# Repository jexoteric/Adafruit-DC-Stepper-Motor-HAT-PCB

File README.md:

# Raspberry Pi Zero DC and Stepper motor hat
Creating a more compact version of the Adafruit DC Stepper motor hat, with the goal of 100% compatability. The only real changes are there is no prototyping area or breakout of the pi pins. Optionally, the four extra PWM pins are now set up to control servos, using a seperate 5V power supply.

Programming with this board should be 100% identical to programming with the original Adafruit design linked below.

For more details, check out the product page at

   * https://www.adafruit.com/products/2348

Adafruit invests time and resources providing this open source design, 
please support Adafruit and open-source hardware by purchasing 
products from Adafruit!

Original board designed by Adafruit Industries.  
Creative Commons Attribution, Share-Alike license, check license.txt for more information
All text above must be included in any redistribution

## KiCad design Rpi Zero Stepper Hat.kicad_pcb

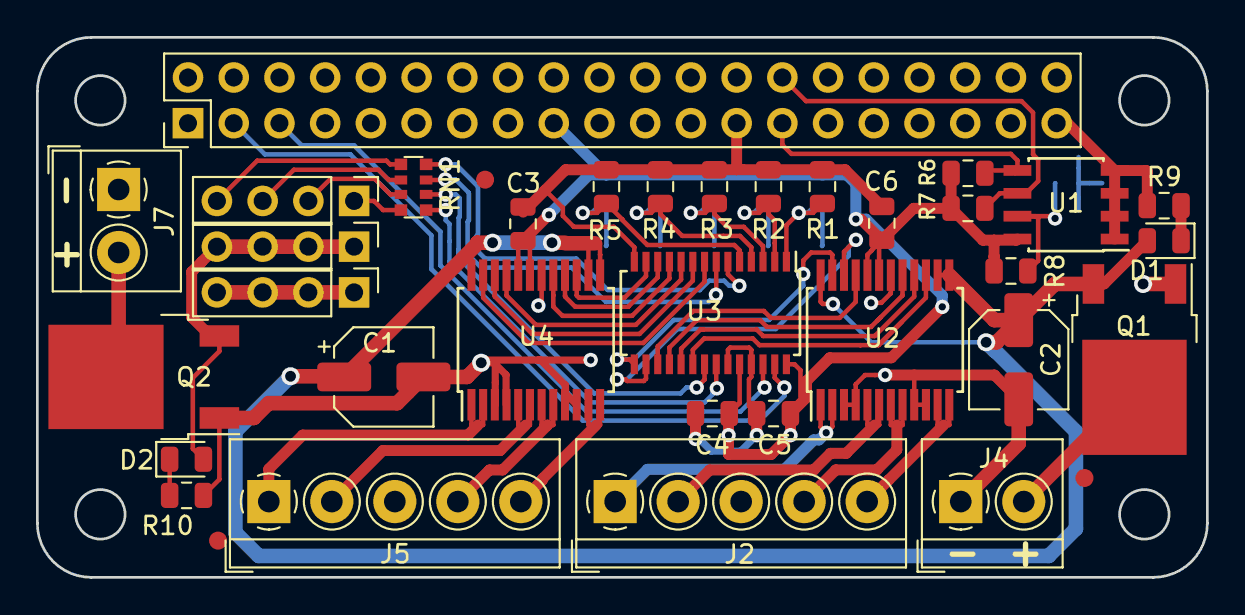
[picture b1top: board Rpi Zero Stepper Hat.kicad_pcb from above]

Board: 2 copper layers, 65.0 x 30.0 mm, 44 parts (0 on the bottom side), 46 nets.

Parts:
+: Conn_01x05_Male; PinHeader_1x04_P2.54mm_Vertical
C1, C2: 47uF/16v; CP_Elec_5x5.4
C3, C6: 10uF; C_0805_2012Metric
C4, C5: 0.1uF; C_0805_2012Metric
D1, D2: GREEN; D_0805_2012Metric
G: Conn_01x04_Male; PinHeader_1x04_P2.54mm_Vertical
J1: Raspberry_Pi_2_3; PinHeader_2x20_P2.54mm_Vertical
J2, J5: Screw_Terminal_01x05; TerminalBlock_4Ucon_1x05_P3.50mm_Horizontal
J3: Conn_01x04_Male; PinHeader_1x04_P2.54mm_Vertical
J4, J7: Screw_Terminal_01x02; TerminalBlock_4Ucon_1x02_P3.50mm_Horizontal
JP1, JP2, JP3, JP4, JP5: SolderJumper_2_Open; SolderJumper-2_P1.3mm_Open_Pad1.0x1.5mm
JP6: SolderJumper_2_Bridged; SolderJumper-2_P1.3mm_Bridged_RoundedPad1.0x1.5mm
Q1, Q2: AOD417; TO-252-2
R1, R2, R3, R4, R5: 10K; R_0805_2012Metric
R6, R7, R8: 3.9K; R_0805_2012Metric
R9: 1K; R_0805_2012Metric
R10: 300; R_0805_2012Metric
RN1: R_Pack04; R_Array_Convex_4x0612
TP1, TP2, TP3, TP4, TP5: TestPoint; TestPoint_Pad_D2.0mm
U1: CAT24C32; SOIC-8_3.9x4.9mm_P1.27mm
U2, U4: TB6612FNG; SSOP-24_5.3x8.2mm_P0.65mm
U3: PCA9685PW; TSSOP-28_4.4x9.7mm_P0.65mm

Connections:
+3V3: C3.1, C4.1, C5.1, C6.1, J1.1, J1.17, JP1.2, JP2.2, JP3.2, JP4.2, JP5.2, R6.2, R7.1, R8.1, U1.8, U2.19, U2.20, U3.24, U3.28, U4.19, U4.20
+5V: +.1, +.2, +.3, +.4, D2.2, J1.2, J1.4, Q2.3
+12V: C1.1, C2.1, D1.2, Q1.3, U2.13, U2.14, U2.24, U4.13, U4.14, U4.24
A0: JP1.1, R1.1, TP1.1, U3.1
A1: JP2.1, R2.1, TP2.1, U3.2
A2: JP3.1, R3.1, TP3.1, U3.3
A3: JP4.1, R4.1, TP4.1, U3.4
A4: JP5.1, R5.1, TP5.1, U3.5
EECLOCK: J1.28, R7.2, U1.6
EEDATA: J1.27, R6.1, U1.5
GND: C1.2, C2.2, C3.2, C4.2, C5.2, C6.2, G.1, G.2, G.3, G.4, J1.6, J1.9, J1.14, J1.20, J1.25, J1.30, J1.34, J1.39, J2.3, J4.1, J5.3, J7.1, JP6.2, Q1.1, Q2.1, R1.2, R2.2, R3.2, R4.2, R5.2, R9.2, R10.2, U1.1, U1.2, U1.3, U1.4, U2.3, U2.4, U2.9, U2.10, U2.18, U3.14, U3.23, U3.25, U4.3, U4.4, U4.9, U4.10, U4.18
unnamed: D1.1, R9.1
unnamed: D2.1, R10.1
unnamed: J2.1, U2.1, U2.2
unnamed: J2.2, U2.5, U2.6
unnamed: J2.4, U2.7, U2.8
unnamed: J2.5, U2.11, U2.12
unnamed: J3.1, RN1.1
unnamed: J3.2, RN1.2
unnamed: J3.3, RN1.3
unnamed: J3.4, RN1.4
unnamed: J4.2, Q1.2
unnamed: J5.1, U4.1, U4.2
unnamed: J5.2, U4.5, U4.6
unnamed: J5.4, U4.7, U4.8
unnamed: J5.5, U4.11, U4.12
unnamed: J7.2, Q2.2
unnamed: JP6.1, R8.2, U1.7
PWM0: RN1.8, U3.6
PWM1: RN1.7, U3.7
PWM2: U3.8, U4.23
PWM3: U3.9, U4.22
PWM4: U3.10, U4.21
PWM5: U3.11, U4.17
PWM6: U3.12, U4.16
PWM7: U3.13, U4.15
PWM8: U2.23, U3.15
PWM9: U2.22, U3.16
PWM10: U2.21, U3.17
PWM11: U2.17, U3.18
PWM12: U2.16, U3.19
PWM13: U2.15, U3.20
PWM14: RN1.6, U3.21
PWM15: RN1.5, U3.22
SCL: J1.5, U3.26
SDA: J1.3, U3.27

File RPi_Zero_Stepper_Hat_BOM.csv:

Manufacturer Part Number,Manufacturer,Digi-Key Part Number,Customer Reference,Reference Designator,Packaging,Quantity,Unit Price,Extended Price,Description
EEE-1CA470WAR,Panasonic Electronic Components,PCE4588CT-ND,47uF/16v,"C1, C2",Cut Tape (CT),2,0.38,$0.76,CAP ALUM 47UF 20% 16V SMD
CC0805ZKY5V6BB106,Yageo,311-1355-1-ND,10uF,"C3, C6",Cut Tape (CT),2,0.28,$0.56,CAP CER 10UF 10V Y5V 0805
CC0805ZRY5V9BB104,Yageo,311-1361-1-ND,0.1uF,"C4, C5",Cut Tape (CT),2,0.13,$0.26,CAP CER 0.1UF 50V Y5V 0805
17-21SYGC/S530-E2/TR8,Everlight Electronics Co Ltd,1080-1500-1-ND,GREEN,"D1, D2",Cut Tape (CT),2,0.3,$0.60,LED YELLOW/GREEN CLEAR 0805 SMD
AOD417,Alpha & Omega Semiconductor Inc.,785-1106-1-ND,AOD417,"Q1,Q2",Cut Tape (CT),2,0.56,$1.12,MOSFET P-CH 30V 25A TO252
RNCF0805DTE10K0,Stackpole Electronics Inc,RNCF0805DTE10K0CT-ND,10K,"R1, R2, R3, R4, R5",Cut Tape (CT),5,0.17,$0.85,RES 10K OHM 0.5% 1/8W 0805
RC0805FR-073K9L,Yageo,311-3.90KCRCT-ND,3.9K,"R6, R7, R8",Cut Tape (CT),3,0.1,$0.30,RES SMD 3.9K OHM 1% 1/8W 0805
RNCP0805FTD1K00,Stackpole Electronics Inc,RNCP0805FTD1K00CT-ND,1K,R9,Cut Tape (CT),1,0.1,$0.10,RES 1K OHM 1% 1/4W 0805
CAT24C32WI-GT3,ON Semiconductor,CAT24C32WI-GT3CT-ND,CAT24C32,U1,Cut Tape (CT),1,0.2,$0.20,IC EEPROM 32K I2C 1MHZ 8SOIC
"TB6612FNG,C,8,EL",Toshiba Semiconductor and Storage,TB6612FNGC8ELCT-ND,TB6612FNG,"U2, U4",Cut Tape (CT),2,2.11,$4.22,IC MOTOR DRIVER 2.7V-5.5V 24SSOP
"PCA9685PW,118",NXP USA Inc.,568-11925-1-ND,PCA9685PW,U3,Cut Tape (CT),1,2.33,$2.33,IC LED DRIVER RGBA 28-TSSOP
30035,SCS,SCP417-ND,ESD Bag,,Bag,1,0.11,$0.11,"BAG 3X5"" ZIP STATIC SHIELD 1=1EA"
SSQ-120-03-T-D,Samtec Inc.,SAM1204-20-ND,Stacking Header,,Bulk,1,3.53,$3.53,CONN RCPT 40POS 0.1 TIN PCB
ED555/2DS,On Shore Technology Inc.,ED1514-ND,Terminal Block 2pos,"J4, J7",Box,2,1.06,$2.12,TERM BLK 2POS SIDE ENT 3.5MM PCB
ED555/5DS,On Shore Technology Inc.,ED1517-ND,Terminal Block 5pos,"J2, J5",Bulk,2,1.72,$3.44,TERM BLK 5POS SIDE ENT 3.5MM PCB
EXB-38V221JV,Panasonic Electronic Components,Y9221CT-ND,Resistor Network,RN1,Cut Tape (CT),1,0.1,$0.10,RES ARRAY 4 RES 220 OHM 1206
RC0805JR-07300RL,Yageo,311-300ARCT-ND,300 ohm resistor,R10,Cut Tape (CT),1,0.1,$0.10,RES SMD 300 OHM 5% 1/8W 0805

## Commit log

2019-01-10 Add KiCAD Schematic
    Recreated the schematic in KiCAD using all native symbols.
2019-04-02 V2 with 4x servo connections
    Revised design to use the extra pwm pins for servos with independent power input
2019-04-02 Added part number list as CSV file
2019-04-02 Add Gerber Files and pictures
